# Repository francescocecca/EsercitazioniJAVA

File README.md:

# Esercizi-Java
Repository in cui è contenuta la soluzione di alcuni esercizi svolti durante il corso di Programmazione ad Oggetti 2021/20222

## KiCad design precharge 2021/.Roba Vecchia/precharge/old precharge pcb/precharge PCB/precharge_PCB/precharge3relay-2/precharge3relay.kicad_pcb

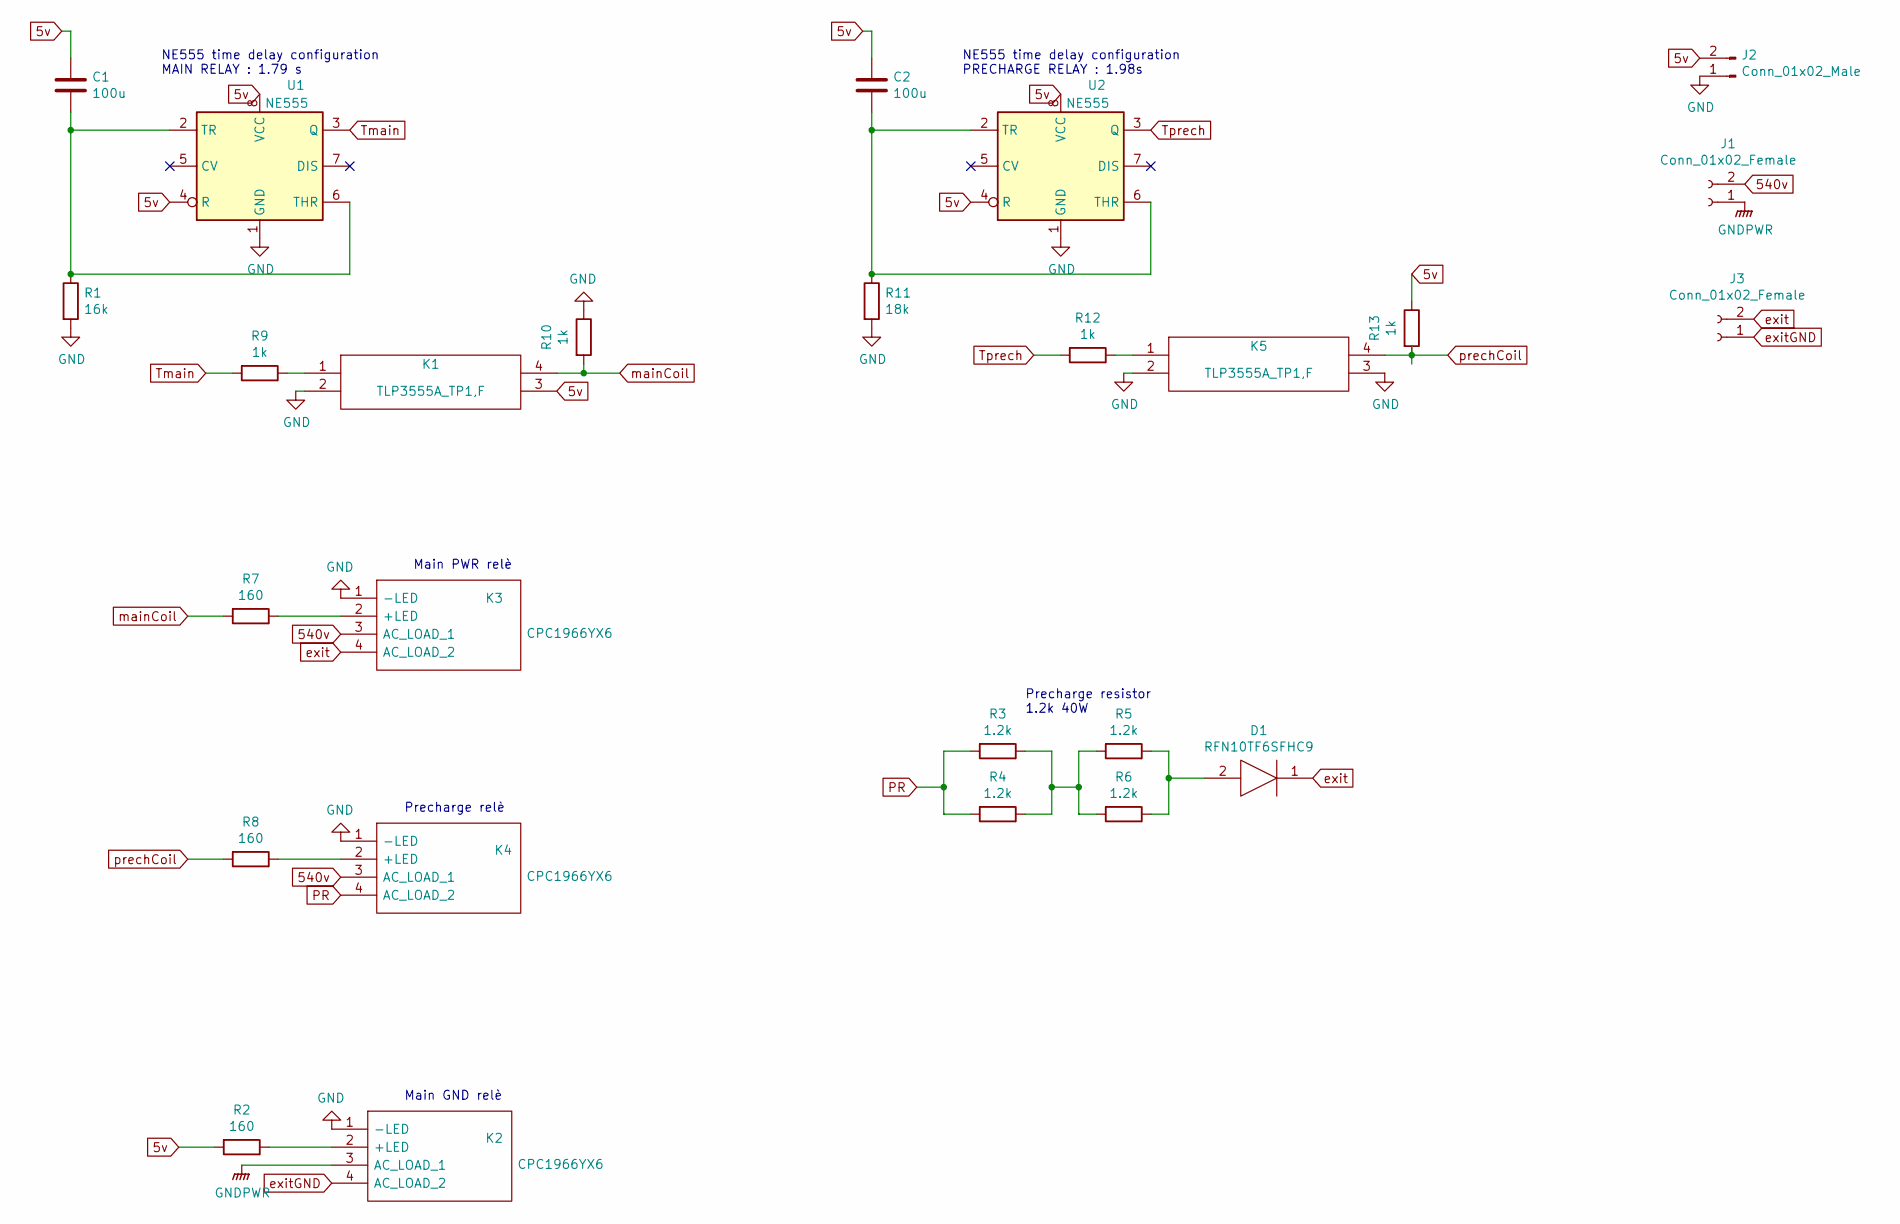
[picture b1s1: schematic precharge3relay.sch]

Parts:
C1, C2: 100u; C_0603_1608Metric_Pad1.05x0.95mm_HandSolder
D1: RFN10TF6SFHC9; TO508P480X1010X1840-2P; Mouser Part Number 755-RFN10TF6SFHC9
J1, J3: Conn_01x02_Female; PhoenixContact_MC_1,5_2-G-5.08_1x02_P5.08mm_Horizontal
J2: Conn_01x02_Male; JST_PH_S2B-PH-K_1x02_P2.00mm_Horizontal
K1, K5: TLP3555A_TP1,F; DIP762W60P254L458H485Q4N; Mouser Part Number 757-TLP3555A(TP1,F
K2, K3, K4: CPC1966YX6; Mouser Part Number 849-CPC1966YX6
R1: 16k; R_0603_1608Metric_Pad1.05x0.95mm_HandSolder
R2, R7, R8: 160; R_0603_1608Metric_Pad1.05x0.95mm_HandSolder
R3, R4, R5, R6: 1.2k; R_Axial_DIN0207_L6.3mm_D2.5mm_P7.62mm_Horizontal
R9, R10, R12, R13: 1k; R_0603_1608Metric_Pad1.05x0.95mm_HandSolder
R11: 18k; R_0603_1608Metric_Pad1.05x0.95mm_HandSolder
U1, U2: NE555; DIP-8_W7.62mm_SMDSocket_SmallPads

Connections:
5v: C1.1, C2.1, J2.2, K1.3, R2.2, R13.1, U1.4 (R), U1.8 (VCC), U2.4 (R), U2.8 (VCC)
540v: J1.2, K3.3 (AC_LOAD_1), K4.3 (AC_LOAD_1)
GND: J2.1, K1.2, K2.1 (-LED), K3.1 (-LED), K4.1 (-LED), K5.2, K5.3, R1.2, R10.1, R11.2, U1.1 (GND), U2.1 (GND)
GNDPWR: J1.1, K2.3 (AC_LOAD_1)
unnamed: C1.2, R1.1, U1.2 (TR), U1.6 (THR)
unnamed: C2.2, R11.1, U2.2 (TR), U2.6 (THR)
unnamed: D1.2, R5.1, R6.1
unnamed: K1.1, R9.1
unnamed: K2.2 (+LED), R2.1
unnamed: K3.2 (+LED), R7.1
unnamed: K4.2 (+LED), R8.1
unnamed: K5.1, R12.1
unnamed: R3.1, R4.1, R5.2, R6.2
PR: K4.4 (AC_LOAD_2), R3.2, R4.2
Tmain: R9.2, U1.3 (Q)
Tprech: R12.2, U2.3 (Q)
exit: D1.1, J3.2, K3.4 (AC_LOAD_2)
exitGND: J3.1, K2.4 (AC_LOAD_2)
mainCoil: K1.4, R7.2, R10.2
prechCoil: K5.4, R8.2, R13.2

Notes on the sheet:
Precharge resistor 1.2k 40W
NE555 time delay configuration PRECHARGE RELAY : 1.98s
NE555 time delay configuration MAIN RELAY : 1.79 s
Main PWR relè
Precharge relè
Main GND relè

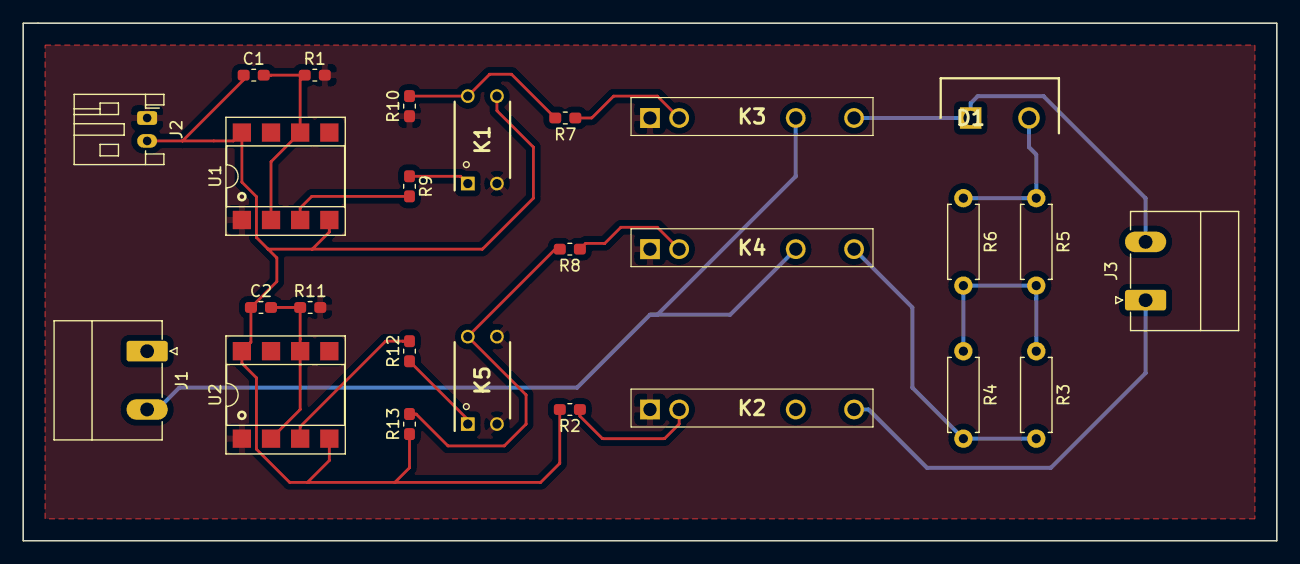
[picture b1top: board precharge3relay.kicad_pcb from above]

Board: 2 copper layers, 109.2 x 45.1 mm, 26 parts (0 on the bottom side), 20 nets.

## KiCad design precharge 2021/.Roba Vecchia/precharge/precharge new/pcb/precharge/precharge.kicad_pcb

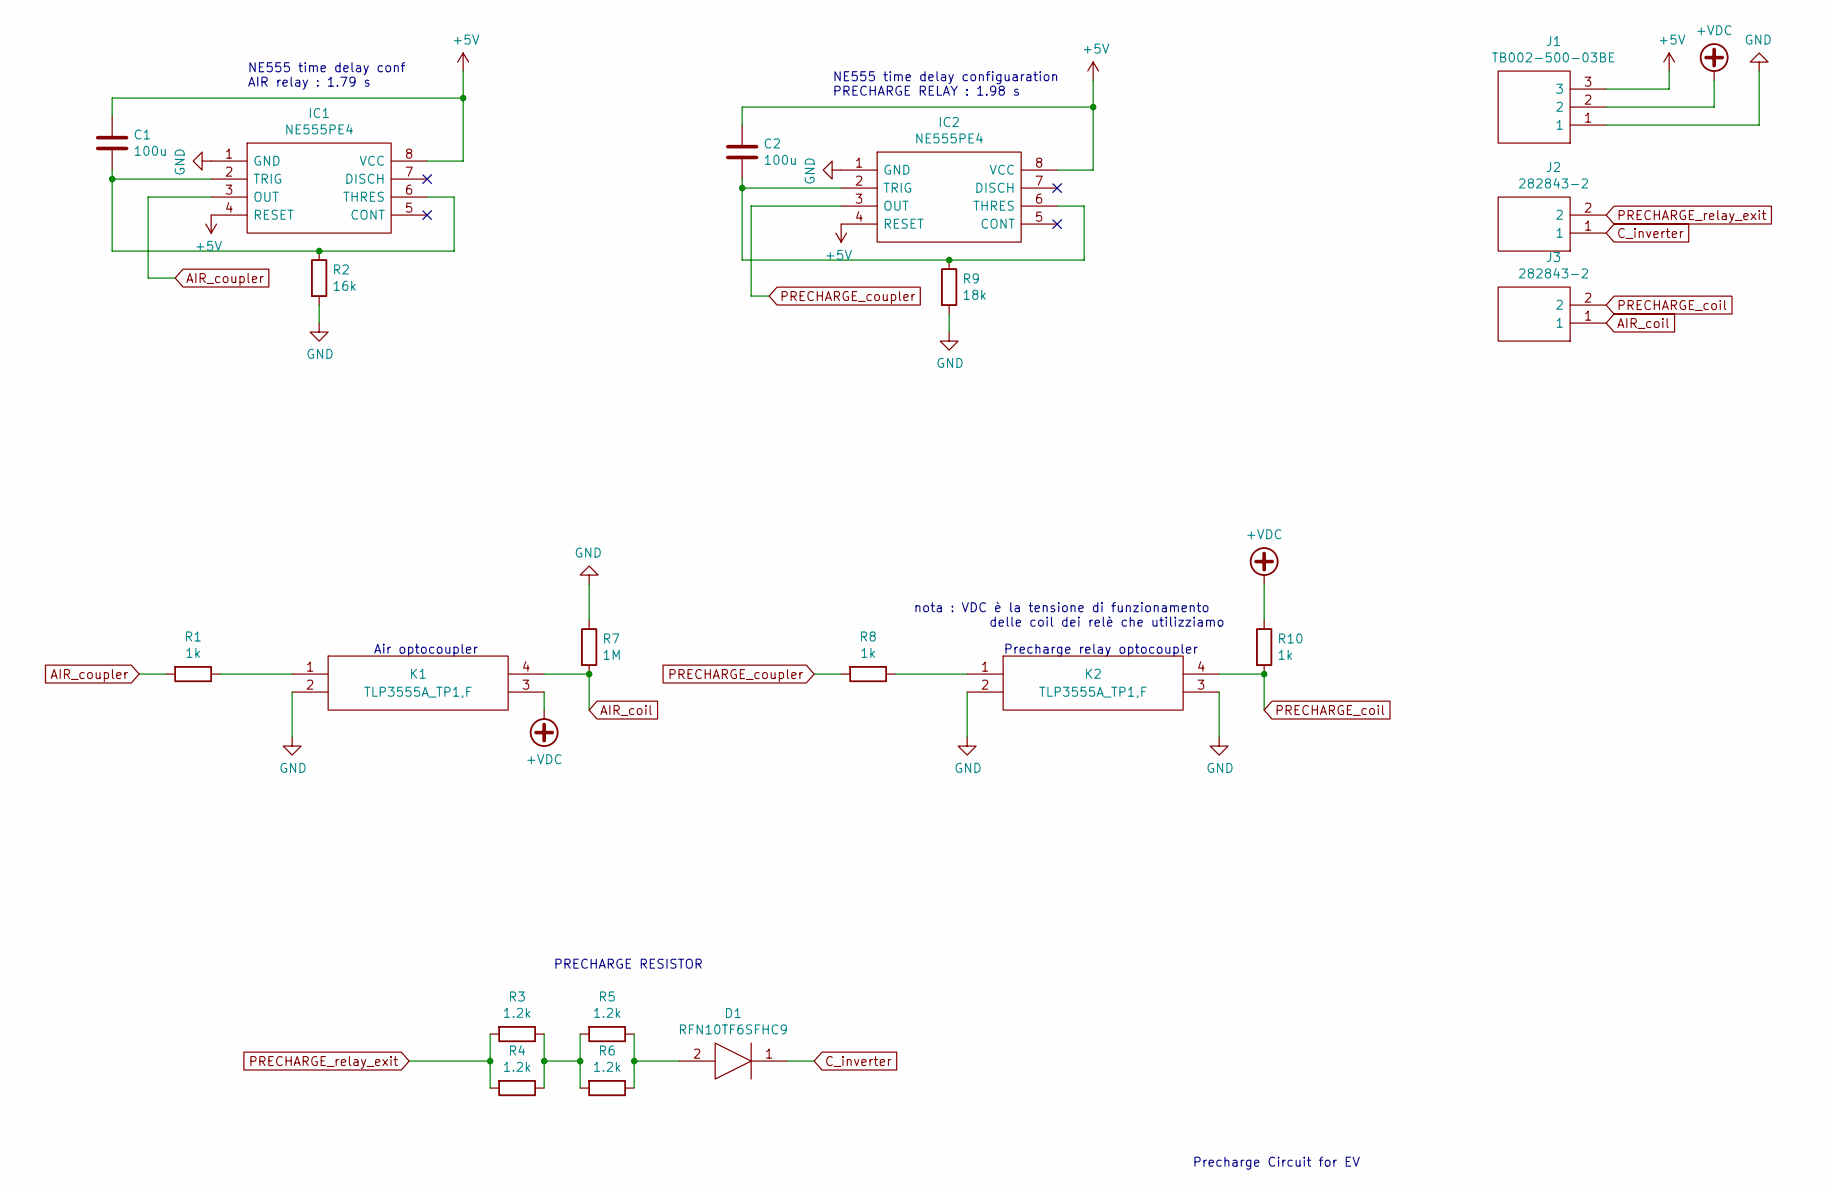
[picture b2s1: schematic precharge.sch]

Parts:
C1, C2: 100u; C_0201_0603Metric
D1: RFN10TF6SFHC9; TO508P480X1010X1840-2P; Mouser Part Number 755-RFN10TF6SFHC9
IC1, IC2: NE555PE4; DIP794W53P254L959H508Q8N; Mouser Part Number 595-NE555PE4
J1: TB002-500-03BE; SHDR3W100P0X500_1X3_1500X760X1000P; Mouser Part Number 490-TB002-500-03BE
J2, J3: 282843-2; SHDR2W130P0X1016_1X2_1524X900X1550P; Mouser Part Number 571-282843-2
K1, K2: TLP3555A_TP1,F; DIP762W60P254L458H485Q4N; Mouser Part Number 757-TLP3555A(TP1,F
R1: 1k; R_0201_0603Metric
R2: 16k; R_0402_1005Metric
R3, R4, R5, R6: 1.2k; R_Axial_DIN0207_L6.3mm_D2.5mm_P15.24mm_Horizontal
R7: 1M; R_0402_1005Metric
R8, R10: 1k; R_0402_1005Metric
R9: 18k; R_0402_1005Metric

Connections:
+5V: C1.1, C2.1, IC1.4 (RESET), IC1.8 (VCC), IC2.4 (RESET), IC2.8 (VCC), J1.3
+VDC: J1.2, K1.3, R10.1
AIR_coil: J3.1, K1.4, R7.2
AIR_coupler: IC1.3 (OUT), R1.2
C_inverter: D1.1, J2.1
GND: IC1.1 (GND), IC2.1 (GND), J1.1, K1.2, K2.2, K2.3, R2.2, R7.1, R9.2
unnamed: C1.2, IC1.2 (TRIG), IC1.6 (THRES), R2.1
unnamed: C2.2, IC2.2 (TRIG), IC2.6 (THRES), R9.1
unnamed: D1.2, R5.1, R6.1
unnamed: K1.1, R1.1
unnamed: K2.1, R8.1
unnamed: R3.1, R4.1, R5.2, R6.2
PRECHARGE_coil: J3.2, K2.4, R10.2
PRECHARGE_coupler: IC2.3 (OUT), R8.2
PRECHARGE_relay_exit: J2.2, R3.2, R4.2

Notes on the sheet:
NE555 time delay conf AIR relay : 1.79 s
Precharge Circuit for EV
nota : VDC è la tensione di funzionamento delle coil dei relè che utilizziamo
Air optocoupler
Precharge relay optocoupler
PRECHARGE RESISTOR
NE555 time delay configuaration PRECHARGE RELAY : 1.98 s

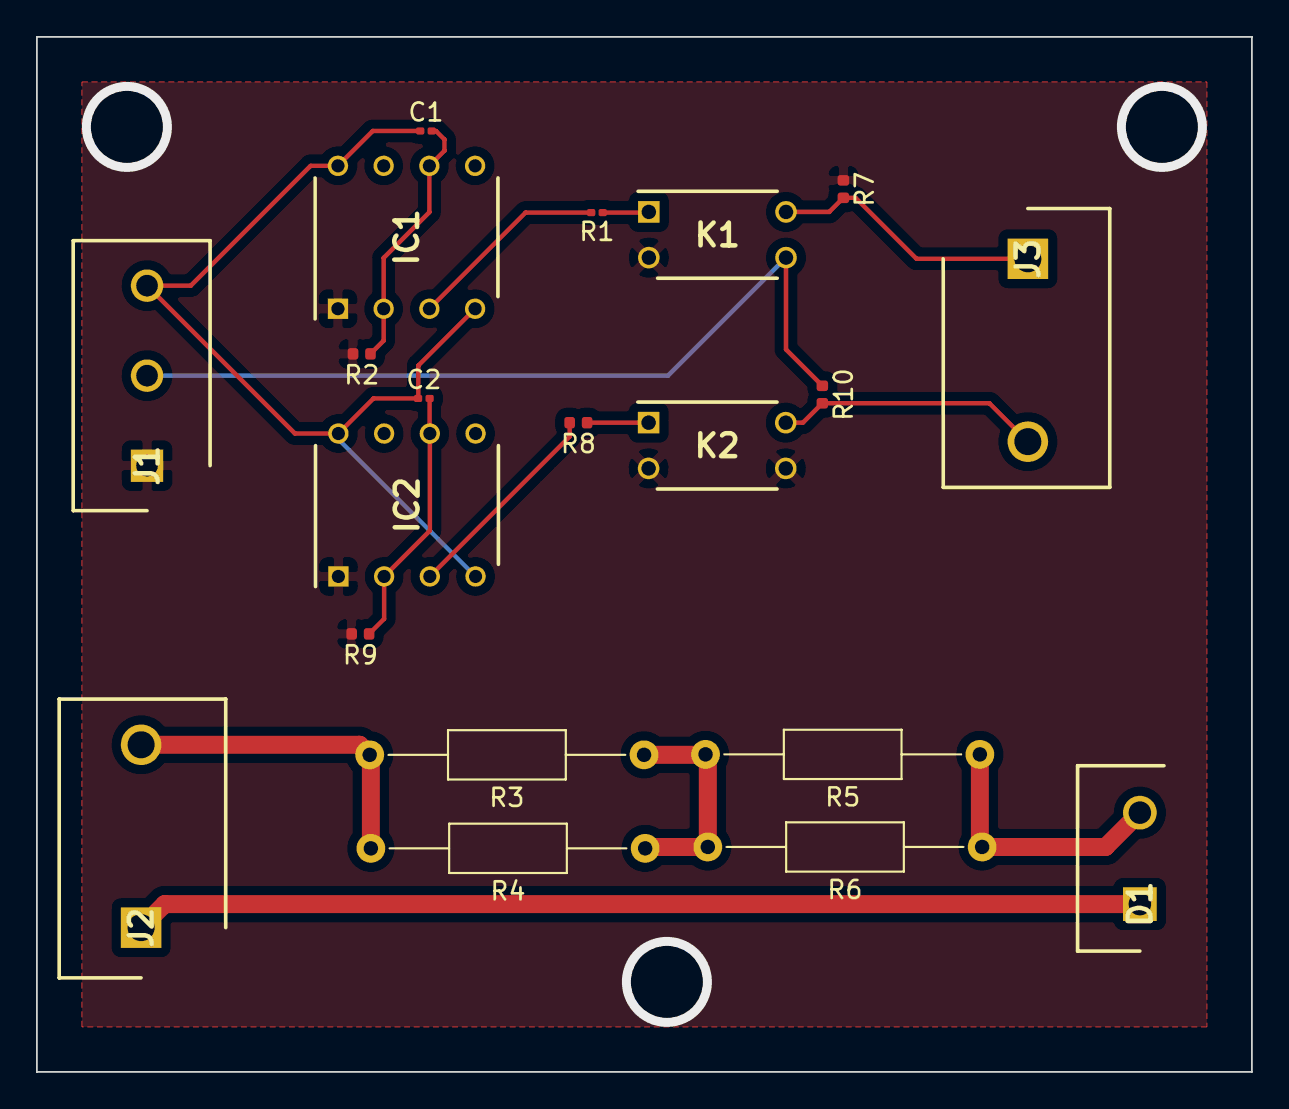
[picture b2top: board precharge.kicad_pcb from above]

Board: 2 copper layers, 67.5 x 57.5 mm, 20 parts (0 on the bottom side), 15 nets.

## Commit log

2021-11-16 Aggiunta progetto precharge
2021-12-02 Update Folder Name
2021-12-02 Update Repository
2021-12-03 Add SpringaBoot example
2021-12-03 Add Restaurant Project
2021-12-03 Update Restaurant Example
2021-12-03 Aggiornamento
